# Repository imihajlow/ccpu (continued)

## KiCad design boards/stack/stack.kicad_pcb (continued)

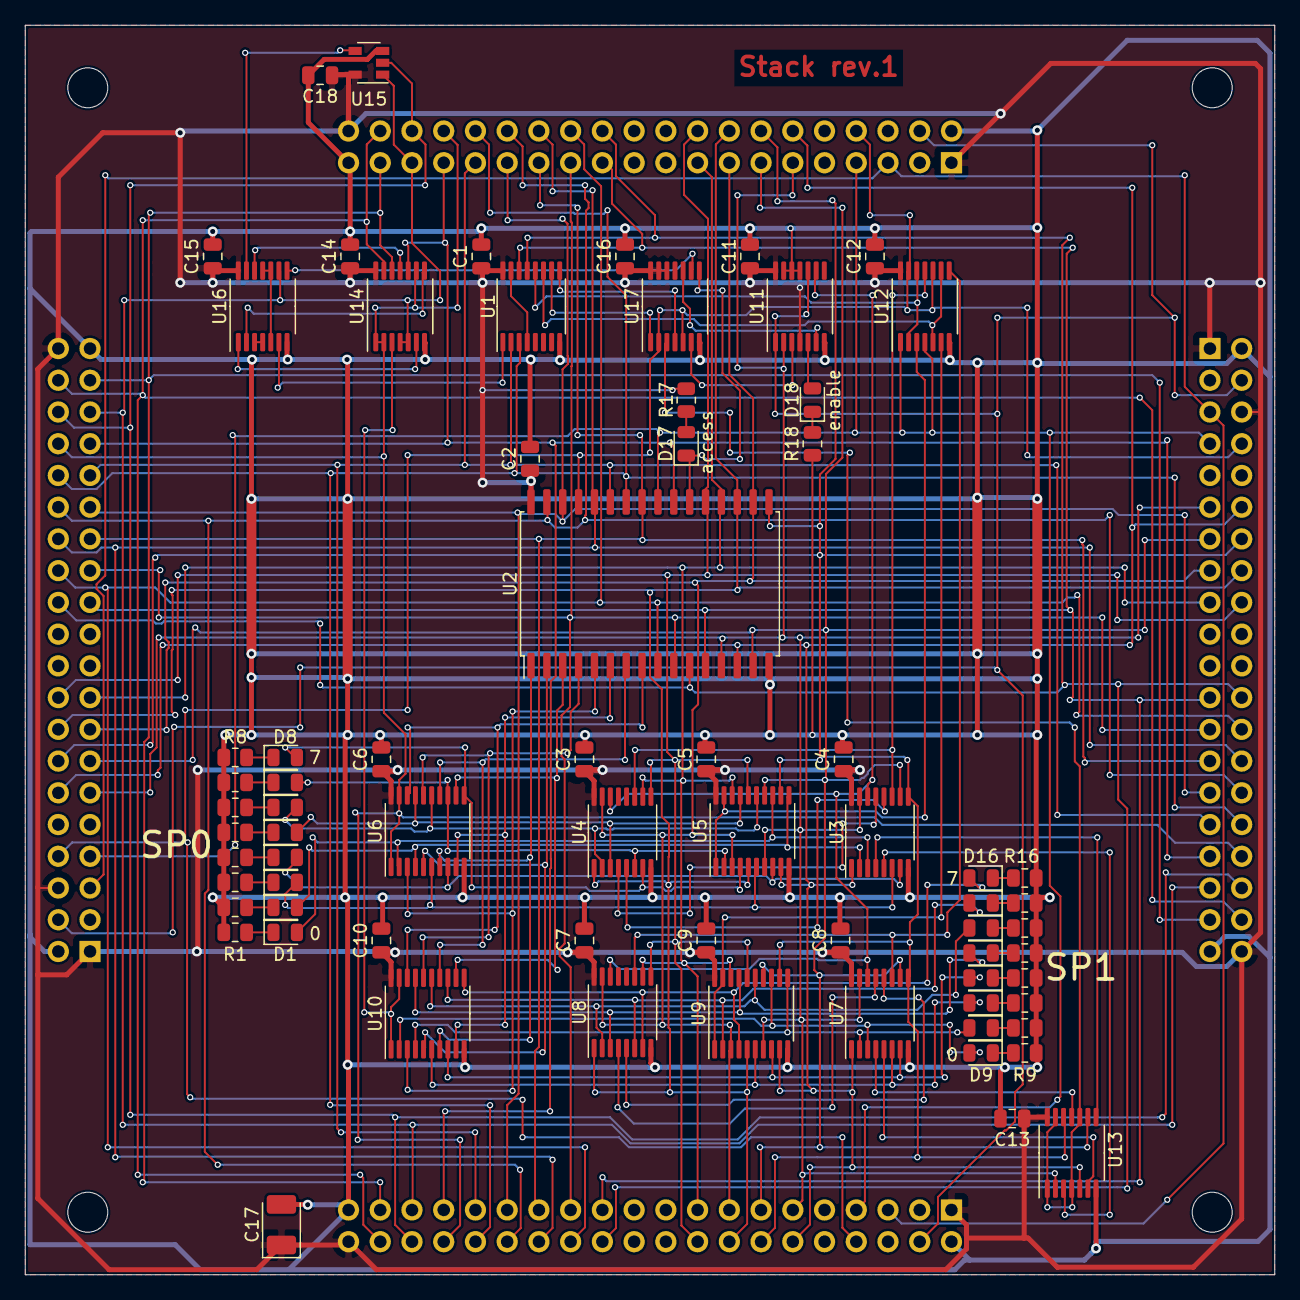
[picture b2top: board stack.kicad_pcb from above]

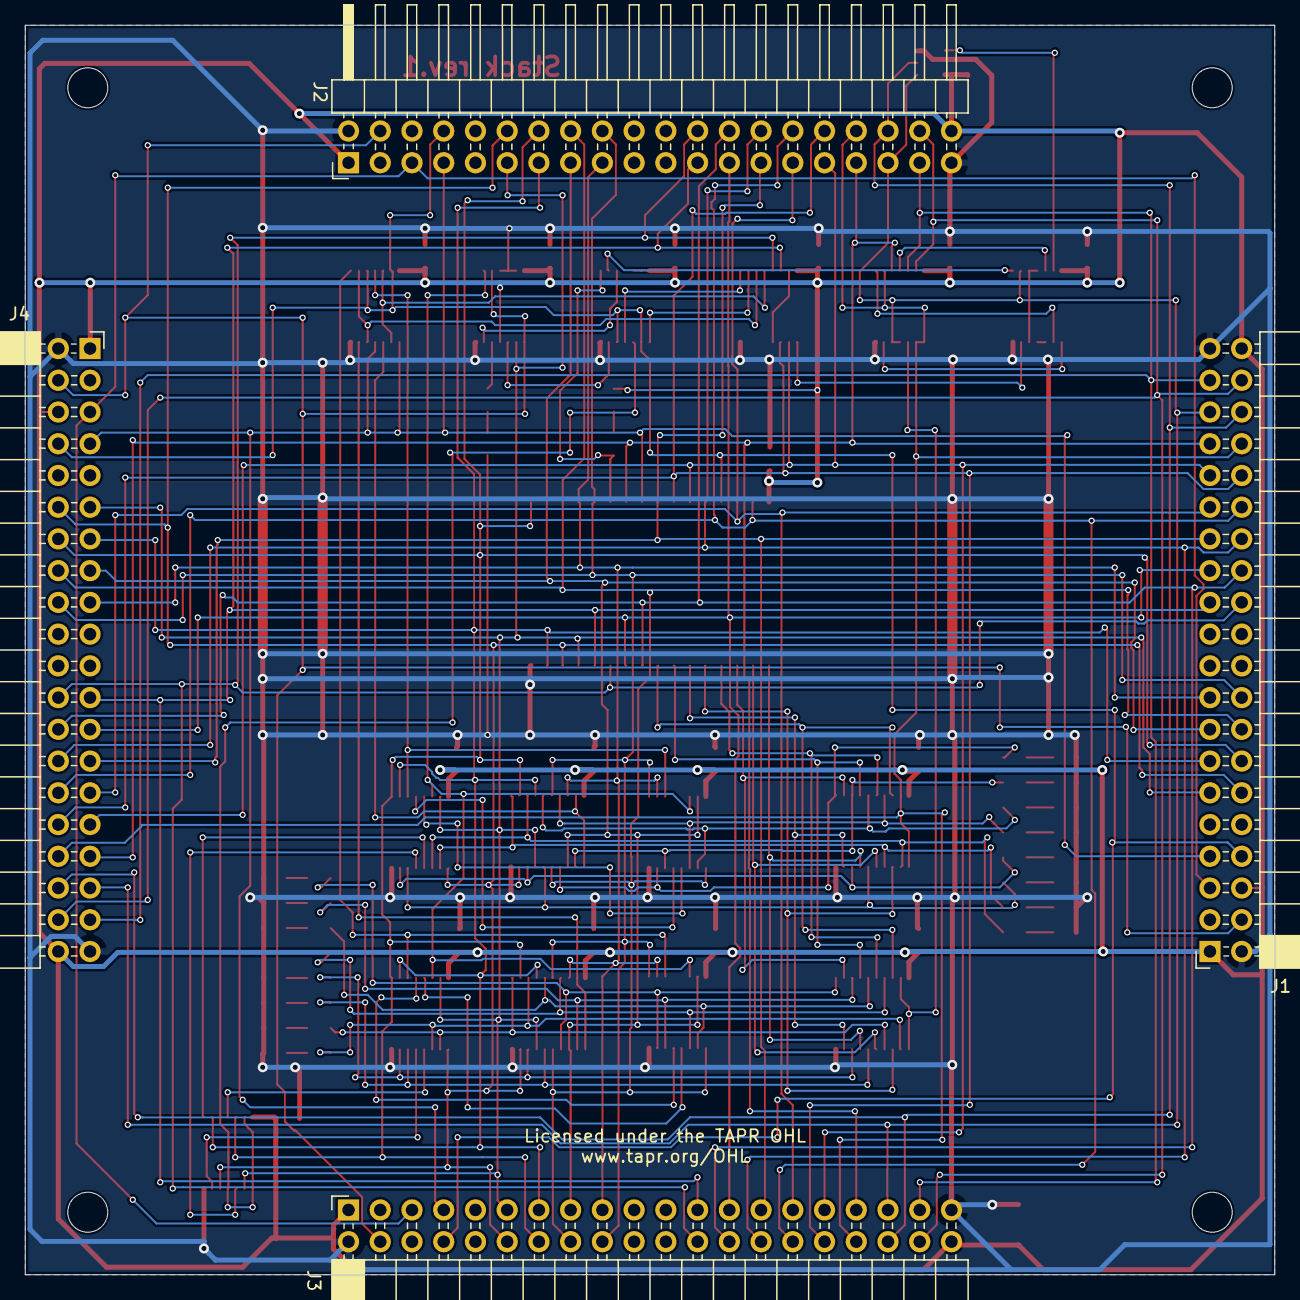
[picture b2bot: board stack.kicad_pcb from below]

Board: 2 copper layers, 100.0 x 100.0 mm, 79 parts (4 on the bottom side), 104 nets.

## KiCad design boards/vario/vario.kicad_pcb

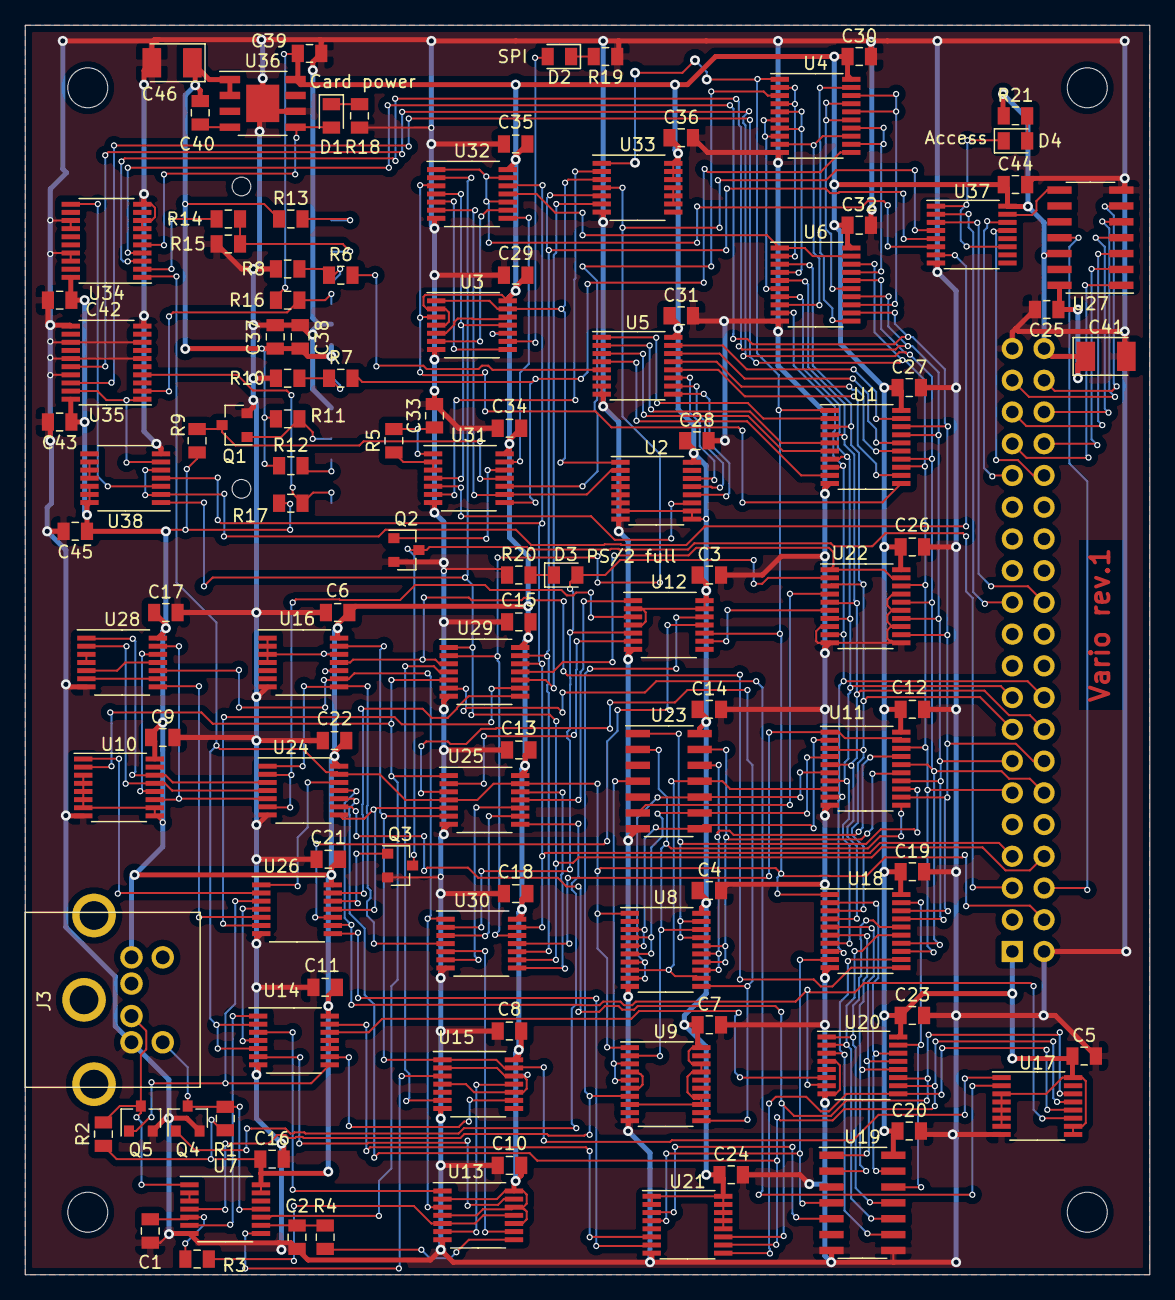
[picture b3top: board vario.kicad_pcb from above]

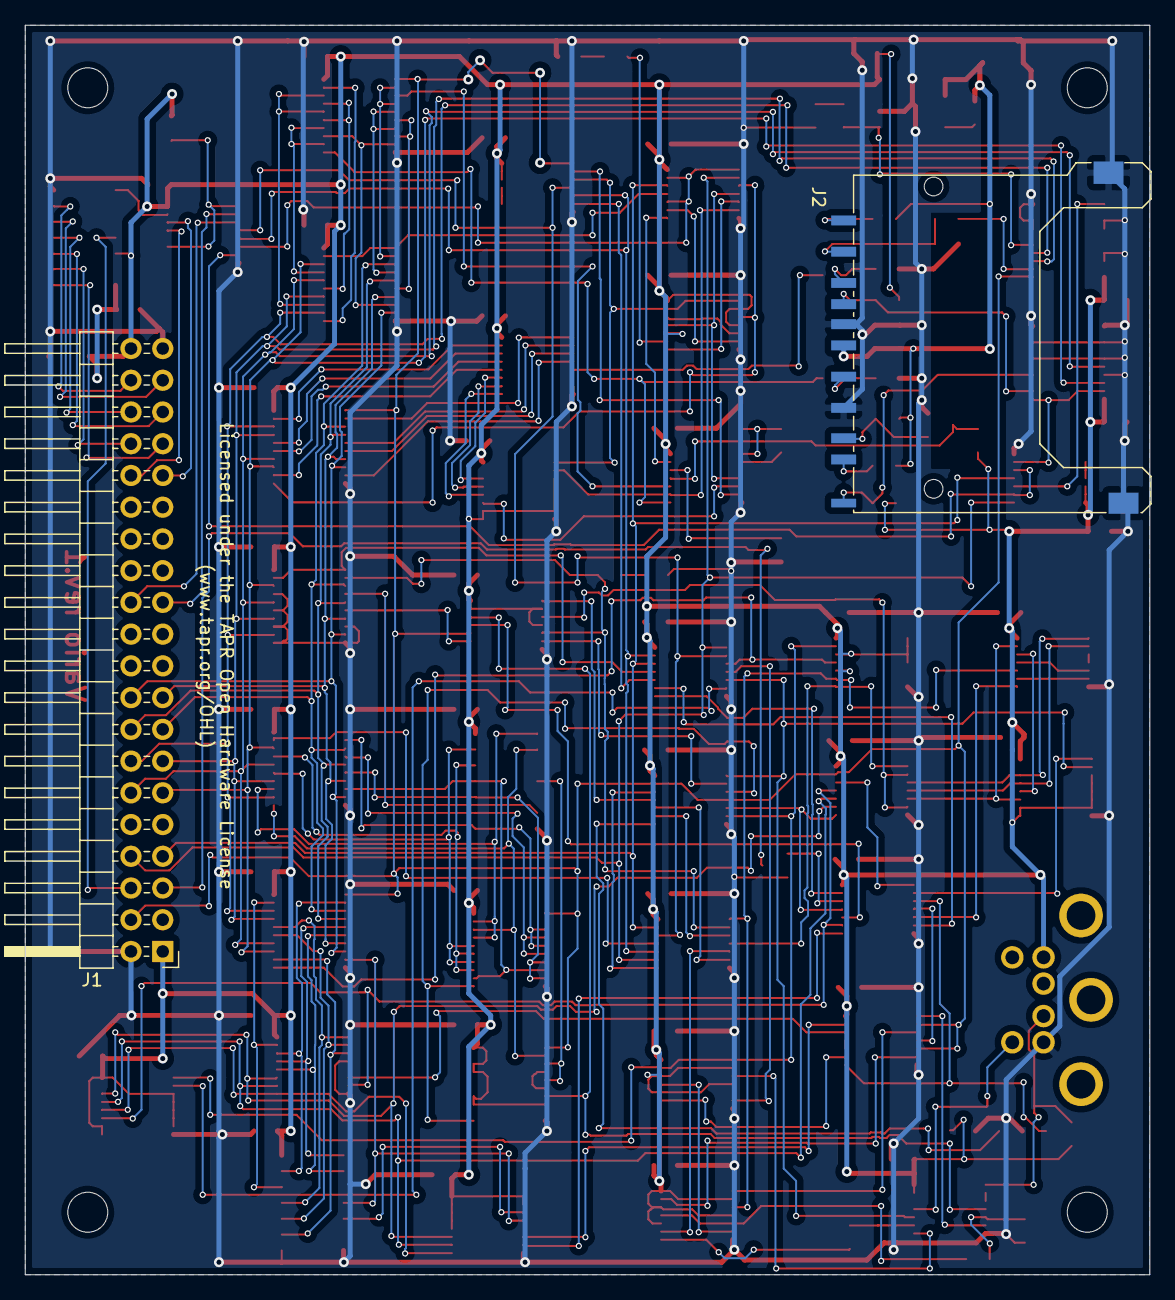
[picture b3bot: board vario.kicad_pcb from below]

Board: 2 copper layers, 90.0 x 100.0 mm, 121 parts (2 on the bottom side), 169 nets.

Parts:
C1, C2, C33: C; C_0805_2012Metric
C3, C4, C5, C6, C7, C8, C9, C10, C11, C12, C13, C14, C15, C16, C17, C18, C19, C20, C21, C22, C23, C24, C25, C26, C27, C28, C29, C30, C31, C32, C34, C35, C36, C37, C42, C43, C44, C45: 0.1; C_0805_2012Metric
C38, C39: 1.0; C_0805_2012Metric
C40: 10n; C_0805_2012Metric
C41, C46: 33.0x10v; CP_EIA-3528-21_Kemet-B_Pad1.50x2.35mm_HandSolder
D1, D2, D3, D4: LED; LED_0805_2012Metric
H1, H2, H3, H4: MountingHole; MountingHole_3.2mm_M3
J1: Conn_02x20_Odd_Even; PinHeader_2x20_P2.54mm_Horizontal
J2: SD_Card; SD_Kyocera_145638009211859+
J3: Mini-DIN-6; Connector-MiniDIN-6
Q1, Q2, Q3, Q4, Q5: 2N7002; SOT-23
R1, R2: 1k; R_0805_2012Metric
R3, R4, R5: R; R_0805_2012Metric
R6, R7, R9, R14: 10k; R_0805_2012Metric
R8, R10, R15: 20k; R_0805_2012Metric
R11, R12, R13, R16, R17: 47k; R_0805_2012Metric
R18, R19, R20, R21: 620; R_0805_2012Metric
U1, U4, U8, U9, U18, U34: 74HC273PW; TSSOP-20_4.4x6.5mm_P0.65mm
U2, U10, U17: 74HC161PW; TSSOP-16_4.4x5mm_P0.65mm
U3, U12, U13, U15, U16: 74HC74PW; TSSOP-14_4.4x5mm_P0.65mm
U5, U20, U21: MC74HC151ADTR2G; TSSOP-16_4.4x5mm_P0.65mm
U6, U11, U22, U35: MC74HC244ADT; TSSOP-20_4.4x6.5mm_P0.65mm
U7, U31: SN74LV14APW; TSSOP-14_4.4x5mm_P0.65mm
U14, U25, U33: 74HC08PW; TSSOP-14_4.4x5mm_P0.65mm
U19, U23: CD74HC280MT; SOIC-14_3.9x8.7mm_P1.27mm
U24: SN74LV10APW; TSSOP-14_4.4x5mm_P0.65mm
U26: 74HC04PW; TSSOP-14_4.4x5mm_P0.65mm
U27: 74HC30D; SOIC-14_3.9x8.7mm_P1.27mm
U28, U29, U30, U32, U38: SN74HC32PWR; TSSOP-14_4.4x5mm_P0.65mm
U36: IFX54441EJV33; Infineon_PG-DSO-8-27_3.9x4.9mm_EP2.65x3mm
U37: SN74HC139PW; TSSOP-16_4.4x5mm_P0.65mm

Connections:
+3V3: C37.1, C38.1, C40.1, C46.1, J2.4, R11.1, R12.1, R13.1, U36.1, U36.2
/SPI/clk: R7.2, U4.11, U31.8
/SPI/clk_ena: D2.2, U3.9
/SPI/count0: U2.14, U5.11
/SPI/count1: U2.13, U5.10
/SPI/count2: U2.12, U5.9
/SPI/count3: U2.11, U31.5
/SPI/int_clk: R5.1, U31.2, U31.3
/SPI/miso: U4.3, U31.10
/SPI/mosi: R6.2, U5.5
/SPI/rdy_int: U3.6, U32.9
/SPI/rdy_out: U31.13, U32.8
/SPI/reg_recv_q0: U4.2, U4.4, U6.2
/SPI/reg_recv_q1: U4.5, U4.7, U6.4
/SPI/reg_recv_q2: U4.6, U4.8, U6.6
/SPI/reg_recv_q3: U4.9, U4.13, U6.8
/SPI/reg_recv_q4: U4.12, U4.14, U6.17
/SPI/reg_recv_q5: U4.15, U4.17, U6.15
/SPI/reg_recv_q6: U4.16, U4.18, U6.13
/SPI/reg_recv_q7: U4.19, U6.11
/SPI/reg_send_cp: U1.11, U3.3, U32.3
/SPI/reg_send_q0: U1.12, U5.12
/SPI/reg_send_q1: U1.15, U5.13
/SPI/reg_send_q2: U1.16, U5.14
/SPI/reg_send_q3: U1.19, U5.15
/SPI/reg_send_q4: U1.2, U5.1
/SPI/reg_send_q5: U1.5, U5.2
/SPI/reg_send_q6: U1.6, U5.3
/SPI/reg_send_q7: U1.9, U5.4
/SPI/~clk: U2.2, U31.9, U32.6
/SPI/~clk_ena: U3.8, U32.5
/SPI/~count3: U31.6, U33.2
/SPI/~int_clk: U3.11, U31.4, U32.4
/SPI/~int_rst: U2.1, U3.1, U3.13, U33.3
/SPI/~oe_to_d: U6.1, U6.19, U32.11
/SPI/~rdy_int: U3.5, U3.12
/SPI/~rdy_out: Q2.1, U31.12
/a0: J1.23, U37.2
/a1: J1.24, U37.3
/a8: J1.31, U37.14
/a9: J1.32, U37.13
/a10: J1.33, U27.1
/a11: J1.34, U27.2
/a12: J1.35, U27.3
/a13: J1.36, U27.4
/a14: J1.37, U27.5
/a15: J1.38, U27.6
/card_ctl_clk: U34.11, U38.3
/d0: J1.11, U1.13, U6.18, U11.18, U18.13, U22.18, U35.18
/d1: J1.12, U1.14, U6.16, U11.16, U18.14, U22.16, U35.16
/d2: J1.13, U1.17, U6.14, U11.14, U18.17, U22.14, U34.3
/d3: J1.14, U1.18, U6.12, U11.12, U18.18, U22.12, U34.4
/d4: J1.15, U1.3, U6.3, U11.3, U18.3, U22.3
/d5: J1.16, U1.4, U6.5, U11.5, U18.4, U22.5
/d6: J1.17, U1.7, U6.7, U11.7, U18.7, U22.7
/d7: J1.18, U1.8, U6.9, U11.9, U18.8, U22.9
/en_3v3: D1.2, U34.5, U36.5
/ena: J1.6, U27.11
/ps2/cnt_recv_rst: U24.12, U26.1
/ps2/common_rdy: U26.6, U29.9
/ps2/data_in: U7.4, U9.7, U12.12
/ps2/data_out: U14.4, U26.4
/ps2/data_out_ena: U14.9, U15.9
/ps2/has_data: D3.2, U12.5, U22.2, U30.2
/ps2/ps2_clk: J3.5, Q4.3, R1.2, U7.11
/ps2/ps2_data: J3.1, Q5.3, R2.2, U7.1
/ps2/rdy_out: U26.13, U29.8
/ps2/recv_byte0: U8.3, U8.5, U11.2, U23.8
/ps2/recv_byte1: U8.4, U8.6, U11.4, U23.9
/ps2/recv_byte2: U8.7, U8.9, U11.6, U23.10
/ps2/recv_byte3: U8.8, U8.12, U11.8, U23.11
/ps2/recv_byte4: U8.13, U8.15, U11.17, U23.12
/ps2/recv_byte5: U8.14, U8.16, U11.15, U23.13
/ps2/recv_byte6: U8.17, U8.19, U11.13, U23.1
/ps2/recv_byte7: U8.18, U9.2, U11.11, U23.2
/ps2/recv_clk: U7.10, U10.2, U25.1, U29.5
/ps2/recv_clk_out: U12.6, U25.2
/ps2/recv_cnt0: U10.14, U24.3, U28.1
/ps2/recv_cnt1: U10.13, U24.4, U28.2
/ps2/recv_cnt2: U10.12, U28.12
/ps2/recv_cnt3: U10.11, U24.5, U28.13
/ps2/recv_full_clk: U12.3, U24.2, U24.6
/ps2/recv_par: U9.3, U9.5, U23.4
/ps2/recv_reg_q10: U9.4, U9.6
/ps2/recv_shift_clk: U8.11, U9.11, U25.3
/ps2/recv_valid: U22.4, U23.6
/ps2/send_ack: U12.9, U22.6
/ps2/send_ack_clk: U12.11, U26.10
/ps2/send_clk_ena_clk: U7.8, U15.3
/ps2/send_clk_out: R4.1, U13.8
/ps2/send_cnt0: U17.14, U20.11, U21.11, U24.9
/ps2/send_cnt1: U17.13, U20.10, U21.10, U24.10
/ps2/send_cnt2: U17.12, U20.9, U21.9
/ps2/send_cnt3: U17.11, U20.7, U24.11, U26.9
/ps2/send_data1: U18.12, U19.9, U20.3
/ps2/send_data2: U18.15, U19.10, U20.2
/ps2/send_data3: U18.16, U19.11, U20.1
/ps2/send_data4: U18.19, U19.12, U20.15
/ps2/send_data5: U18.2, U19.13, U20.14
/ps2/send_data6: U18.5, U19.1, U20.13
/ps2/send_data7: U18.6, U19.2, U20.12
/ps2/send_data8: U18.9, U19.4, U21.4
/ps2/send_ena: U13.3, U16.9, U28.10, U30.1
/ps2/send_ena_clk: U16.11, U18.11, U29.3
/ps2/send_req: R3.1, U13.5, U13.11
/ps2/~clk_out: Q4.1, U25.8
/ps2/~cnt_recv_rst: U10.1, U26.2
/ps2/~common_rdy: U26.5, U28.8
/ps2/~data_in: U7.2, U7.3
/ps2/~data_oe: U11.1, U11.19, U30.11
/ps2/~data_out: Q5.1, U14.8, U26.3
/ps2/~rdy: Q3.1, U26.12
/ps2/~recv_rdy: U28.6, U28.9
/ps2/~recv_rst: U12.1, U25.11
/ps2/~sel: U29.10, U33.6
/ps2/~send_clk: U17.2, U29.6
/ps2/~send_clk_ena: U15.6, U29.4
/ps2/~send_clk_out: U13.9, U30.5
/ps2/~send_clk_out_rst: U13.13, U14.6
/ps2/~send_cnt3: U21.7, U26.8
/ps2/~send_data_out: U14.10, U14.11
/ps2/~send_data_out_hi: U14.13, U21.6
/ps2/~send_data_out_lo: U14.12, U20.6
/ps2/~send_ena: U16.8, U24.1, U30.4
/ps2/~send_ovf: U24.8, U25.5, U26.11
/ps2/~send_req: U13.6, U15.11
/ps2/~send_req_rst: U13.1, U14.3
/ps2/~send_rst: U15.1, U15.13, U16.13, U17.1, U25.6
/ps2/~status_oe: U22.1, U22.19, U29.11
/ps2/~status_we: U25.12, U30.8
/write_protect: J2.11, R17.2, U35.4
/~card_cs: R14.2, U34.2
/~card_cs_3v3: J2.1, R14.1, R15.1
/~card_detect: J2.10, R16.2, U35.2
/~card_status_oe: U35.1, U35.19, U38.6
/~miso: Q1.3, R9.2, U31.11
/~oe: J1.7, U29.12, U30.13, U32.12, U38.4
/~ps2_data_sel: U29.2, U30.12, U33.4, U37.4
/~ps2_status_sel: U29.13, U30.10, U33.5, U37.5
/~spi_ctrl_sel: U37.7, U38.2, U38.5
/~spi_data_sel: U32.1, U32.10, U32.13, U37.6
/~we: J1.8, U29.1, U30.9, U32.2, U38.1
GND: C1.2, C2.2, C3.2, C4.2, C5.2, C6.2, C7.2, C8.2, C9.2, C10.2, C11.2, C12.2, C13.2, C14.2, C15.2, C16.2, C17.2, C18.2, C19.2, C20.2, C21.2, C22.2, C23.2, C24.2, C25.2, C26.2, C27.2, C28.2, C29.2, C30.2, C31.2, C32.2, C33.2, C34.2, C35.2, C36.2, C37.2, C38.2, C39.2, C41.2, C42.2, C43.2, C44.2, C45.2, C46.2, J1.2, J1.39, J2.3, J2.6, J2.12, J2.13, J3.3, Q1.2, Q2.2, Q3.2, Q4.2, Q5.2, R8.2, R10.2, R15.2, R18.1, R19.1, R20.1, U1.10, U2.8, U3.7, U4.10, U5.7, U5.8, U6.10, U7.7, U8.10, U9.10, U10.8, U11.10, U12.7, U13.7, U14.7, U15.7, U16.7, U17.8, U18.10, U19.7, U19.8, U20.4, U20.8, U21.8, U22.8, U22.10, U22.11, U22.13, U22.15, U22.17, U23.7, U24.7, U25.7, U26.7, U27.7, U28.7, U29.7, U30.7, U31.7, U32.7, U33.7, U34.7, U34.8, U34.10, U34.13, U34.14, U34.17, U34.18, U35.6, U35.8, U35.10, U35.11, U35.13, U35.15, U35.17, U36.6, U36.9, U37.8, U38.7
unnamed: C1.1, R3.2, U7.5
unnamed: C2.1, R4.2, U7.9
unnamed: C33.1, R5.2, U31.1
unnamed: C40.2, U36.4
unnamed: D1.1, R18.2
unnamed: D2.1, R19.2
unnamed: D3.1, R20.2
unnamed: D4.1, U37.1, U37.11
unnamed: D4.2, R21.2
unnamed: J2.2, R6.1, R8.1
unnamed: J2.5, R7.1, R10.1
unnamed: J2.7, Q1.1, R11.2
unnamed: J2.8, R12.2
unnamed: J2.9, R13.2
unnamed: U7.6, U14.1
unnamed: U19.5, U21.3
unnamed: U25.9, U30.3
unnamed: U25.10, U30.6
unnamed: U27.8, U37.15
unnamed: U28.3, U28.4
unnamed: U28.5, U28.11
unnamed: U33.9, U33.10, U33.11
unnamed: U38.9, U38.10, U38.11
VCC: C3.1, C4.1, C5.1, C6.1, C7.1, C8.1, C9.1, C10.1, C11.1, C12.1, C13.1, C14.1, C15.1, C16.1, C17.1, C18.1, C19.1, C20.1, C21.1, C22.1, C23.1, C24.1, C25.1, C26.1, C27.1, C28.1, C29.1, C30.1, C31.1, C32.1, C34.1, C35.1, C36.1, C39.1, C41.1, C42.1, C43.1, C44.1, C45.1, J1.1, J1.40, J3.4, R1.1, R2.1, R9.1, R16.1, R17.1, R21.1, U1.20, U2.3, U2.4, U2.5, U2.6, U2.7, U2.9, U2.10, U2.16, U3.2, U3.4, U3.10, U3.14, U4.20, U5.16, U6.20, U7.13, U7.14, U8.20, U9.8, U9.13, U9.14, U9.17, U9.18, U9.20, U10.3, U10.4, U10.5, U10.6, U10.7, U10.9, U10.10, U10.16, U11.20, U12.2, U12.4, U12.13, U12.14, U13.2, U13.4, U13.10, U13.12, U13.14, U14.14, U15.2, U15.4, U15.10, U15.12, U15.14, U16.1, U16.2, U16.3, U16.4, U16.10, U16.12, U16.14, U17.3, U17.4, U17.5, U17.6, U17.7, U17.9, U17.10, U17.16, U18.20, U19.14, U20.16, U21.1, U21.2, U21.12, U21.13, U21.14, U21.15, U21.16, U22.20, U23.14, U24.14, U25.14, U26.14, U27.12, U27.14, U28.14, U29.14, U30.14, U31.14, U32.14, U33.12, U33.13, U33.14, U34.20, U35.20, U36.8, U37.16, U38.12, U38.13, U38.14
rdy: J1.5, Q2.3, Q3.3
~rst: J1.4, U1.1, U4.1, U8.1, U9.1, U12.10, U14.2, U14.5, U18.1, U24.13, U25.4, U25.13, U33.1, U34.1

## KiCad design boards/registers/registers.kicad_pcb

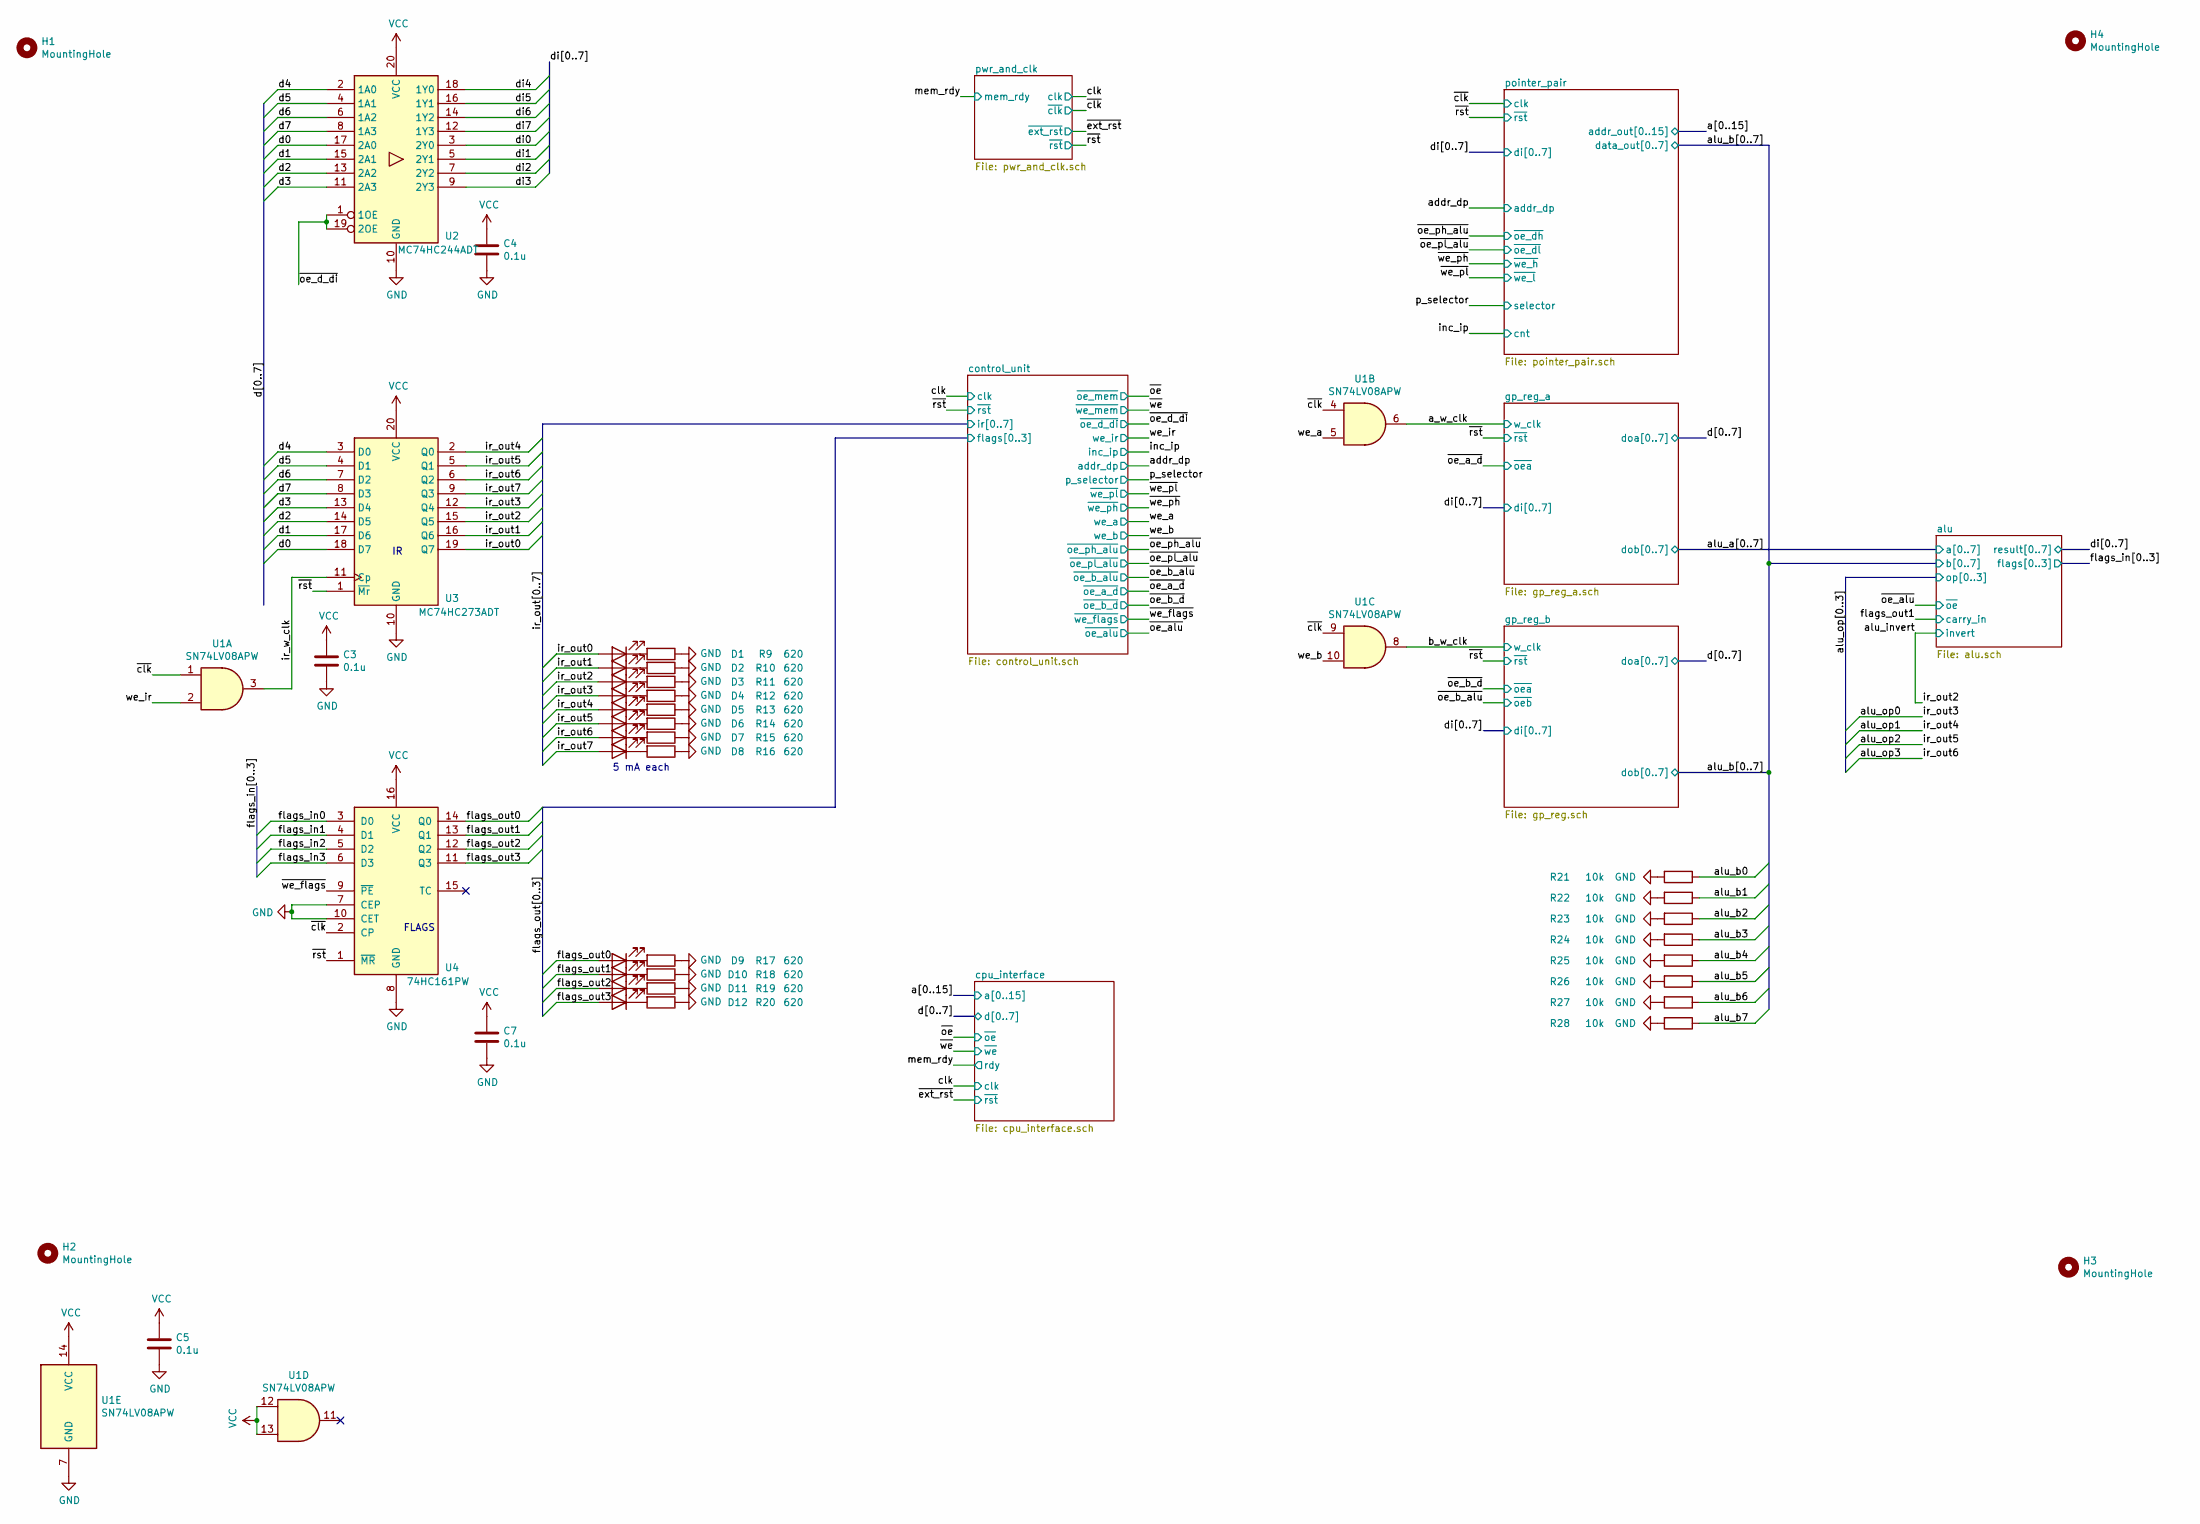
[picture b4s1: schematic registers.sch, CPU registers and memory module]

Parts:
C3, C4, C5, C7: 0.1u; C_0805_2012Metric
D1, D2, D3, D4, D5, D6, D7, D8, D9, D10, D11, D12: KP-2012EC; LED_0805_2012Metric
H1, H2, H3, H4: MountingHole; MountingHole_3.2mm_M3_DIN965
R9, R10, R11, R12, R13, R14, R15, R16, R17, R18, R19, R20: 620; R_0805_2012Metric
R21, R22, R23, R24, R25, R26, R27, R28: 10k; R_0805_2012Metric
U1: SN74LV08APW; TSSOP-14_4.4x5mm_P0.65mm
U2: MC74HC244ADT; TSSOP-20_4.4x6.5mm_P0.65mm
U3: MC74HC273ADT; TSSOP-20_4.4x6.5mm_P0.65mm
U4: 74HC161PW; TSSOP-16_4.4x5mm_P0.65mm

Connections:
/a_w_clk: U1.6; also elsewhere on the board
/alu_b0: R21.1; also elsewhere on the board
/alu_b1: R22.1; also elsewhere on the board
/alu_b2: R23.1; also elsewhere on the board
/alu_b3: R24.1; also elsewhere on the board
/alu_b4: R25.1; also elsewhere on the board
/alu_b5: R26.1; also elsewhere on the board
/alu_b6: R27.1; also elsewhere on the board
/alu_b7: R28.1; also elsewhere on the board
/alu_invert: D3.2 (A), U3.15 (Q5); also elsewhere on the board
/alu_op0: D4.2 (A), U3.12 (Q4); also elsewhere on the board
/alu_op1: D5.2 (A), U3.2 (Q0); also elsewhere on the board
/alu_op2: D6.2 (A), U3.5 (Q1); also elsewhere on the board
/alu_op3: D7.2 (A), U3.6 (Q2); also elsewhere on the board
/b_w_clk: U1.8; also elsewhere on the board
/d0: U2.17 (2A0), U3.18 (D7); also elsewhere on the board
/d1: U2.15 (2A1), U3.17 (D6); also elsewhere on the board
/d2: U2.13 (2A2), U3.14 (D5); also elsewhere on the board
/d3: U2.11 (2A3), U3.13 (D4); also elsewhere on the board
/d4: U2.2 (1A0), U3.3 (D0); also elsewhere on the board
/d5: U2.4 (1A1), U3.4 (D1); also elsewhere on the board
/d6: U2.6 (1A2), U3.7 (D2); also elsewhere on the board
/d7: U2.8 (1A3), U3.8 (D3); also elsewhere on the board
/di0: U2.3 (2Y0); also elsewhere on the board
/di1: U2.5 (2Y1); also elsewhere on the board
/di2: U2.7 (2Y2); also elsewhere on the board
/di3: U2.9 (2Y3); also elsewhere on the board
/di4: U2.18 (1Y0); also elsewhere on the board
/di5: U2.16 (1Y1); also elsewhere on the board
/di6: U2.14 (1Y2); also elsewhere on the board
/di7: U2.12 (1Y3); also elsewhere on the board
/flags_in0: U4.3 (D0); also elsewhere on the board
/flags_in1: U4.4 (D1); also elsewhere on the board
/flags_in2: U4.5 (D2); also elsewhere on the board
/flags_in3: U4.6 (D3); also elsewhere on the board
/flags_out0: D9.2 (A), U4.14 (Q0); also elsewhere on the board
/flags_out1: D10.2 (A), U4.13 (Q1); also elsewhere on the board
/flags_out2: D11.2 (A), U4.12 (Q2); also elsewhere on the board
/flags_out3: D12.2 (A), U4.11 (Q3); also elsewhere on the board
/ir_out0: D1.2 (A), U3.19 (Q7); also elsewhere on the board
/ir_out1: D2.2 (A), U3.16 (Q6); also elsewhere on the board
/ir_out7: D8.2 (A), U3.9 (Q3); also elsewhere on the board
/ir_w_clk: U1.3, U3.11 (Cp)
/we_a: U1.5; also elsewhere on the board
/we_b: U1.10; also elsewhere on the board
/we_ir: U1.2; also elsewhere on the board
/~clk: U1.1, U1.4, U1.9, U4.2 (CP); also elsewhere on the board
/~oe_d_di: U2.1 (1OE), U2.19 (2OE); also elsewhere on the board
/~rst: U3.1 (~Mr), U4.1 (~MR); also elsewhere on the board
/~we_flags: U4.9 (~PE); also elsewhere on the board
GND: C3.2, C4.2, C5.2, C7.2, R9.1, R10.1, R11.1, R12.1, R13.1, R14.1, R15.1, R16.1, R17.1, R18.1, R19.1, R20.1, R21.2, R22.2, R23.2, R24.2, R25.2, R26.2, R27.2, R28.2, U1.7 (GND), U2.10 (GND), U3.10 (GND), U4.7 (CEP), U4.8 (GND), U4.10 (CET); also elsewhere on the board
unnamed: D1.1 (K), R9.2
unnamed: D2.1 (K), R10.2
unnamed: D3.1 (K), R11.2
unnamed: D4.1 (K), R12.2
unnamed: D5.1 (K), R13.2
unnamed: D6.1 (K), R14.2
unnamed: D7.1 (K), R15.2
unnamed: D8.1 (K), R16.2
unnamed: D9.1 (K), R17.2
unnamed: D10.1 (K), R18.2
unnamed: D11.1 (K), R19.2
unnamed: D12.1 (K), R20.2
VCC: C3.1, C4.1, C5.1, C7.1, U1.12, U1.13, U1.14 (VCC), U2.20 (VCC), U3.20 (VCC), U4.16 (VCC); also elsewhere on the board

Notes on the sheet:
5 mA each
FLAGS

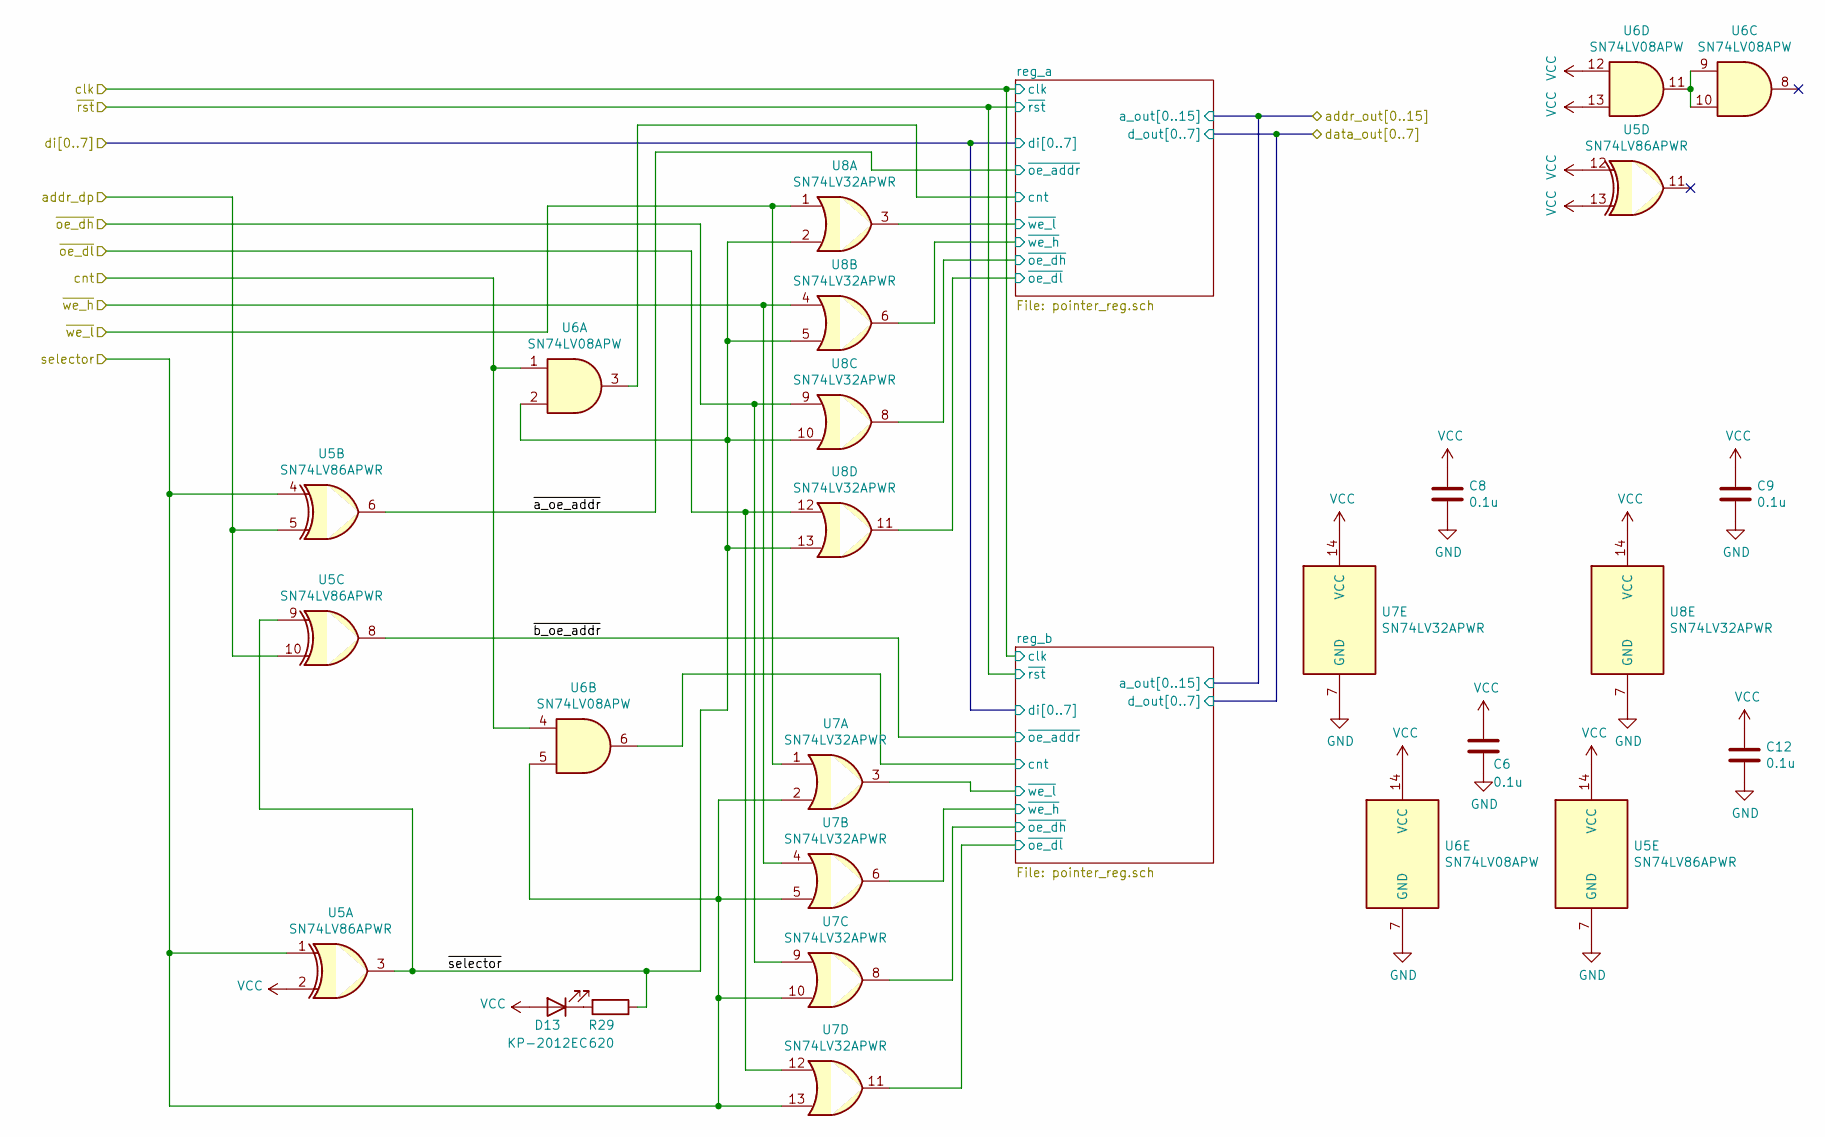
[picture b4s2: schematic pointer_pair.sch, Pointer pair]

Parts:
C6, C8, C9, C12: 0.1u; C_0805_2012Metric
D13: KP-2012EC; LED_0805_2012Metric
R29: 620; R_0805_2012Metric
U5: SN74LV86APWR; TSSOP-14_4.4x5mm_P0.65mm
U6: SN74LV08APW; TSSOP-14_4.4x5mm_P0.65mm
U7, U8: SN74LV32APWR; TSSOP-14_4.4x5mm_P0.65mm

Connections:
/addr_dp: U5.5, U5.10; also elsewhere on the board
/inc_ip: U6.1, U6.4; also elsewhere on the board
/p_selector: U5.1, U5.4, U6.5, U7.2, U7.5, U7.10, U7.13; also elsewhere on the board
/pointer_pair/reg_a/cnt: U6.3; also elsewhere on the board
/pointer_pair/reg_a/~oe_dh: U8.8; also elsewhere on the board
/pointer_pair/reg_a/~oe_dl: U8.11; also elsewhere on the board
/pointer_pair/reg_a/~we_h: U8.6; also elsewhere on the board
/pointer_pair/reg_a/~we_l: U8.3; also elsewhere on the board
/pointer_pair/reg_b/cnt: U6.6; also elsewhere on the board
/pointer_pair/reg_b/~oe_dh: U7.8; also elsewhere on the board
/pointer_pair/reg_b/~oe_dl: U7.11; also elsewhere on the board
/pointer_pair/reg_b/~we_h: U7.6; also elsewhere on the board
/pointer_pair/reg_b/~we_l: U7.3; also elsewhere on the board
/pointer_pair/~a_oe_addr: U5.6; also elsewhere on the board
/pointer_pair/~b_oe_addr: U5.8; also elsewhere on the board
/pointer_pair/~selector: R29.1, U5.3, U5.9, U6.2, U8.2, U8.5, U8.10, U8.13
/~oe_ph_alu: U7.9, U8.9; also elsewhere on the board
/~oe_pl_alu: U7.12, U8.12; also elsewhere on the board
/~we_ph: U7.4, U8.4; also elsewhere on the board
/~we_pl: U7.1, U8.1; also elsewhere on the board
GND: C6.2, C8.2, C9.2, C12.2, U5.7 (GND), U6.7 (GND), U7.7 (GND), U8.7 (GND); also elsewhere on the board
unnamed: D13.1 (K), R29.2
unnamed: U6.9, U6.10, U6.11
VCC: C6.1, C8.1, C9.1, C12.1, D13.2 (A), U5.2, U5.12, U5.13, U5.14 (VCC), U6.12, U6.13, U6.14 (VCC), U7.14 (VCC), U8.14 (VCC); also elsewhere on the board
